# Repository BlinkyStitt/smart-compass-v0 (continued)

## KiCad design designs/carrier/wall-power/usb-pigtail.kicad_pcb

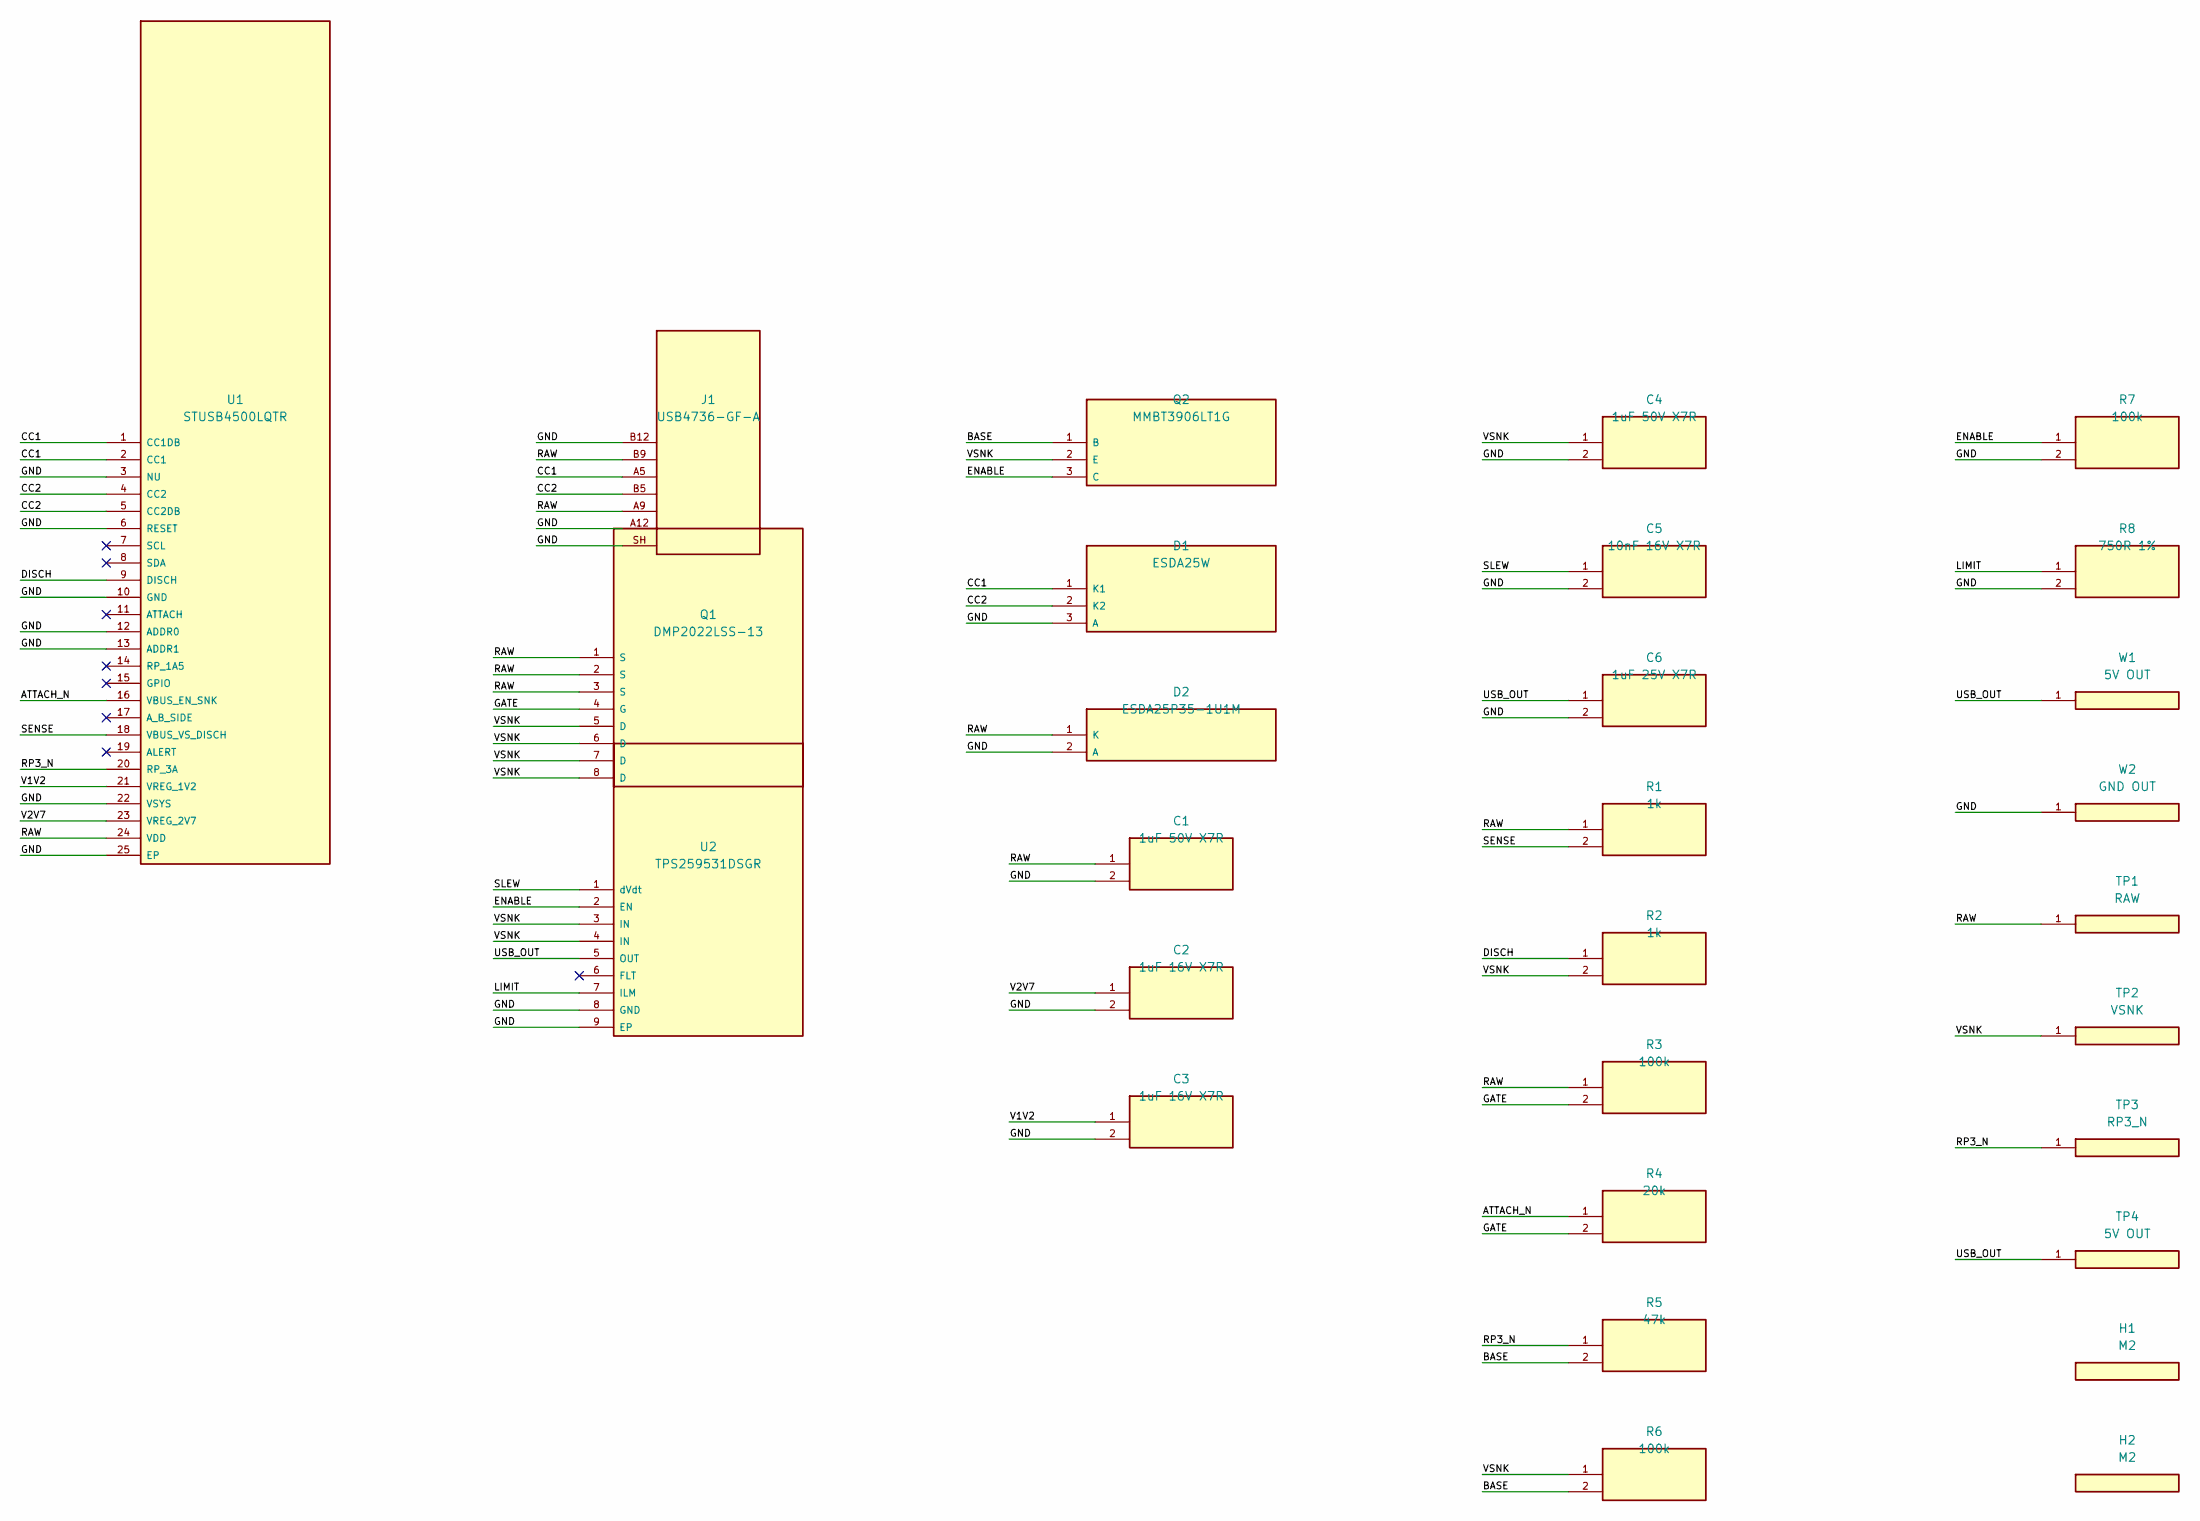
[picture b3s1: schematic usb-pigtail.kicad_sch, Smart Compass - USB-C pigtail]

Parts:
C1, C4: 1uF 50V X7R; C_0805_2012Metric
C2, C3: 1uF 16V X7R; C_0603_1608Metric
C5: 10nF 16V X7R; C_0603_1608Metric
C6: 1uF 25V X7R; C_0805_2012Metric
D1: ESDA25W; SOT-323_SC-70
D2: ESDA25P35-1U1M; ST_QFN-2L_1.6x1mm
H1, H2: M2; MountingHole_2.2mm_M2
J1: USB4736-GF-A
Q1: DMP2022LSS-13; SOIC-8_3.9x4.9mm_P1.27mm
Q2: MMBT3906LT1G; SOT-23
R1, R2: 1k; R_0603_1608Metric
R3, R6, R7: 100k; R_0603_1608Metric
R4: 20k; R_0603_1608Metric
R5: 47k; R_0603_1608Metric
R8: 750R 1%; R_0603_1608Metric
TP1: RAW; TestPoint_Pad_D1.0mm
TP2: VSNK; TestPoint_Pad_D1.0mm
TP3: RP3_N; TestPoint_Pad_D1.0mm
TP4: 5V OUT; TestPoint_Pad_D1.0mm
U1: STUSB4500LQTR; QFN-24-1EP_4x4mm_P0.5mm_EP2.7x2.7mm
U2: TPS259531DSGR; Texas_DSG0008A_WSON-8-1EP_2x2mm_P0.5mm_EP0.9x1.6mm
W1: 5V OUT; Lead_22AWG
W2: GND OUT; Lead_22AWG

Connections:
/ATTACH_N: R4.1, U1.16 (VBUS_EN_SNK)
/BASE: Q2.1 (B), R5.2, R6.2
/CC1: D1.1 (K1), J1.A5, U1.1 (CC1DB), U1.2 (CC1)
/CC2: D1.2 (K2), J1.B5, U1.4 (CC2), U1.5 (CC2DB)
/DISCH: R2.1, U1.9 (DISCH)
/ENABLE: Q2.3 (C), R7.1, U2.2 (EN)
/GATE: Q1.4 (G), R3.2, R4.2
/GND: C1.2, C2.2, C3.2, C4.2, C5.2, C6.2, D1.3 (A), D2.2 (A), J1.A12, J1.B12, J1.SH, R7.2, R8.2, U1.3 (NU), U1.6 (RESET), U1.10 (GND), U1.12 (ADDR0), U1.13 (ADDR1), U1.22 (VSYS), U1.25 (EP), U2.8 (GND), U2.9 (EP), W2.1
/LIMIT: R8.1, U2.7 (ILM)
/RAW: C1.1, D2.1 (K), J1.A9, J1.B9, Q1.1 (S), Q1.2 (S), Q1.3 (S), R1.1, R3.1, TP1.1, U1.24 (VDD)
/RP3_N: R5.1, TP3.1, U1.20 (RP_3A)
/SENSE: R1.2, U1.18 (VBUS_VS_DISCH)
/SLEW: C5.1, U2.1 (dVdt)
/USB_OUT: C6.1, TP4.1, U2.5 (OUT), W1.1
/V1V2: C3.1, U1.21 (VREG_1V2)
/V2V7: C2.1, U1.23 (VREG_2V7)
/VSNK: C4.1, Q1.5 (D), Q1.6 (D), Q1.7 (D), Q1.8 (D), Q2.2 (E), R2.2, R6.1, TP2.1, U2.3 (IN), U2.4 (IN)

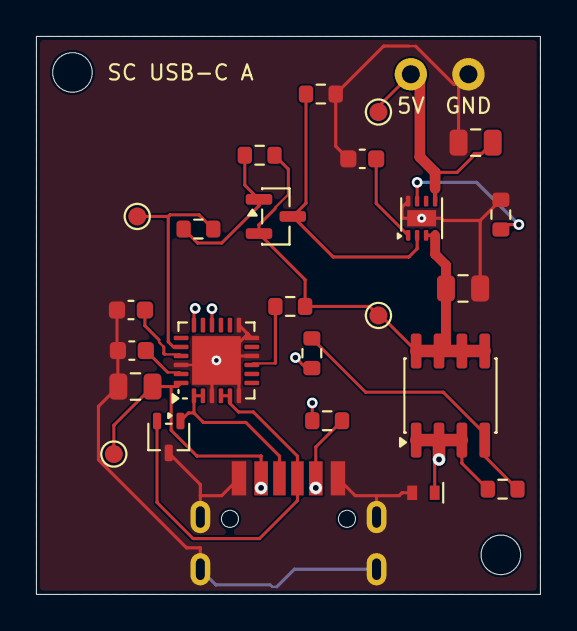
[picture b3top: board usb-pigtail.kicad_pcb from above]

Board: 4 copper layers, 28.0 x 31.0 mm, 29 parts (0 on the bottom side), 17 nets.

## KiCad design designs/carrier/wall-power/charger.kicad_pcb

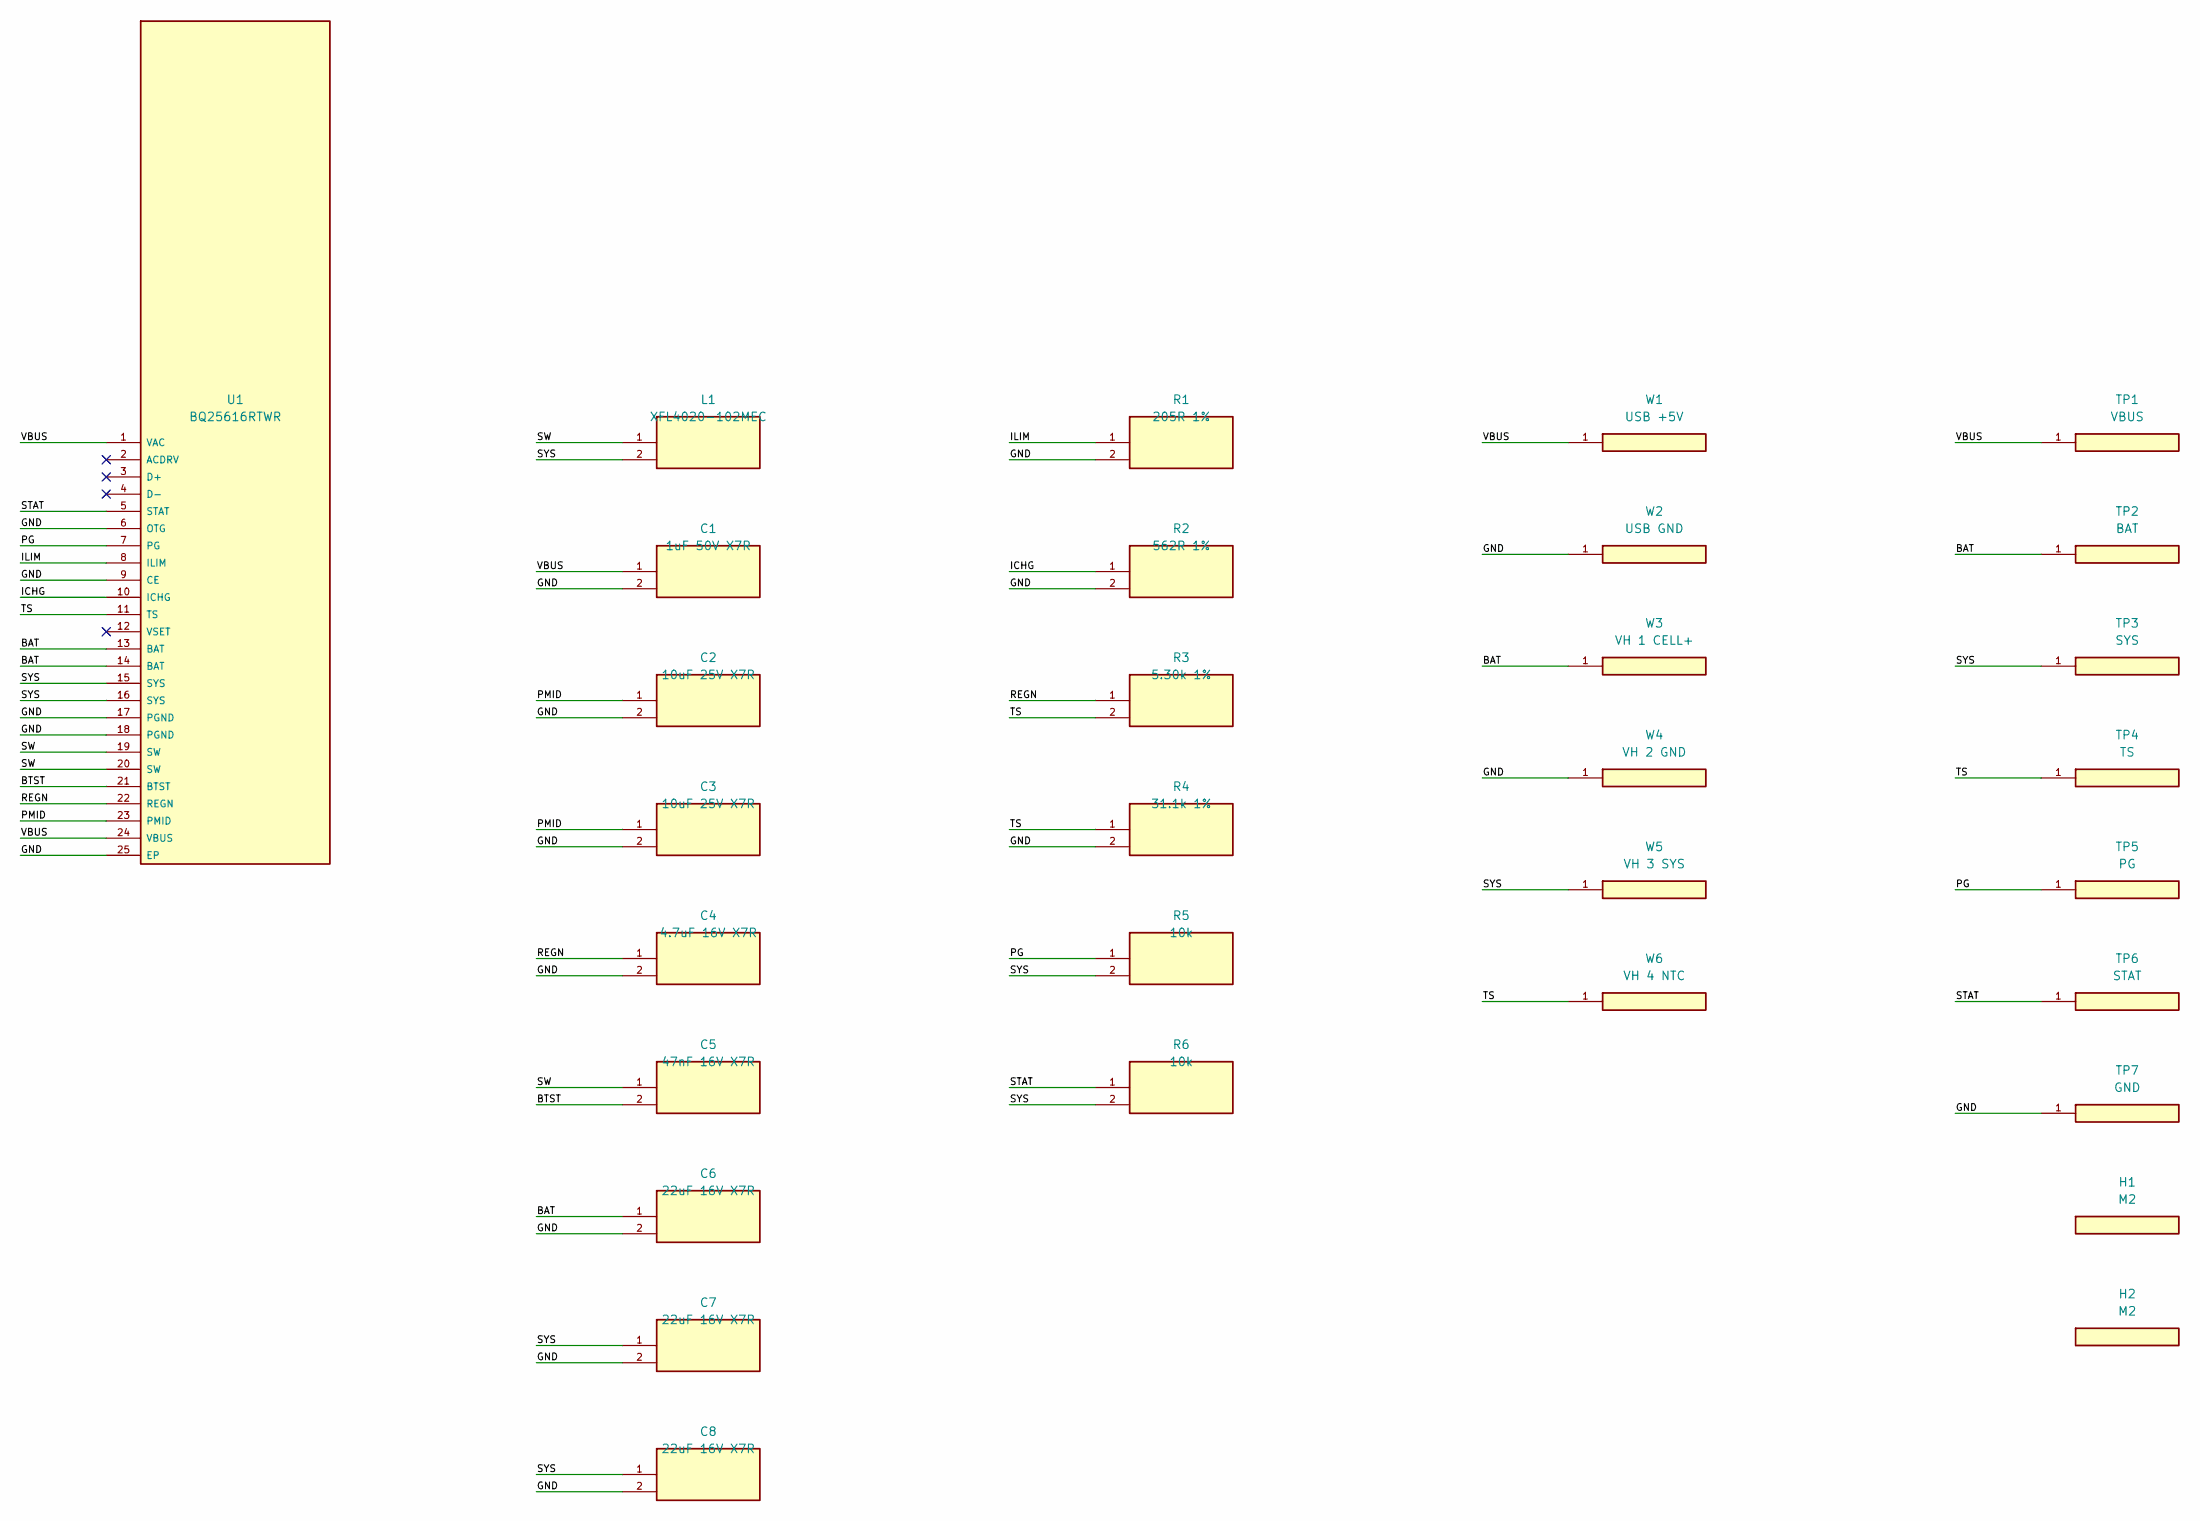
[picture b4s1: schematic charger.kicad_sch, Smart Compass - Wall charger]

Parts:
C1: 1uF 50V X7R; C_0805_2012Metric
C2, C3: 10uF 25V X7R; C_1206_3216Metric
C4: 4.7uF 16V X7R; C_0805_2012Metric
C5: 47nF 16V X7R; C_0603_1608Metric
C6, C7, C8: 22uF 16V X7R; C_1206_3216Metric
H1, H2: M2; MountingHole_2.2mm_M2
L1: XFL4020-102MEC; L_Coilcraft_XxL4020
R1: 205R 1%; R_0603_1608Metric
R2: 562R 1%; R_0603_1608Metric
R3: 5.30k 1%; R_0603_1608Metric
R4: 31.1k 1%; R_0603_1608Metric
R5, R6: 10k; R_0603_1608Metric
TP1: VBUS; TestPoint_Pad_D1.0mm
TP2: BAT; TestPoint_Pad_D1.0mm
TP3: SYS; TestPoint_Pad_D1.0mm
TP4: TS; TestPoint_Pad_D1.0mm
TP5: PG; TestPoint_Pad_D1.0mm
TP6: STAT; TestPoint_Pad_D1.0mm
TP7: GND; TestPoint_Pad_D1.0mm
U1: BQ25616RTWR; Texas_RTW_WQFN-24-1EP_4x4mm_P0.5mm_EP2.7x2.7mm
W1: USB +5V; Lead_22AWG
W2: USB GND; Lead_22AWG
W3: VH 1 CELL+; Lead_22AWG
W4: VH 2 GND; Lead_22AWG
W5: VH 3 SYS; Lead_22AWG
W6: VH 4 NTC; Lead_22AWG

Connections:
/BAT: C6.1, TP2.1, U1.13 (BAT), U1.14 (BAT), W3.1
/BTST: C5.2, U1.21 (BTST)
/GND: C1.2, C2.2, C3.2, C4.2, C6.2, C7.2, C8.2, R1.2, R2.2, R4.2, TP7.1, U1.6 (OTG), U1.9 (CE), U1.17 (PGND), U1.18 (PGND), U1.25 (EP), W2.1, W4.1
/ICHG: R2.1, U1.10 (ICHG)
/ILIM: R1.1, U1.8 (ILIM)
/PG: R5.1, TP5.1, U1.7 (PG)
/PMID: C2.1, C3.1, U1.23 (PMID)
/REGN: C4.1, R3.1, U1.22 (REGN)
/STAT: R6.1, TP6.1, U1.5 (STAT)
/SW: C5.1, L1.1, U1.19 (SW), U1.20 (SW)
/SYS: C7.1, C8.1, L1.2, R5.2, R6.2, TP3.1, U1.15 (SYS), U1.16 (SYS), W5.1
/TS: R3.2, R4.1, TP4.1, U1.11 (TS), W6.1
/VBUS: C1.1, TP1.1, U1.1 (VAC), U1.24 (VBUS), W1.1

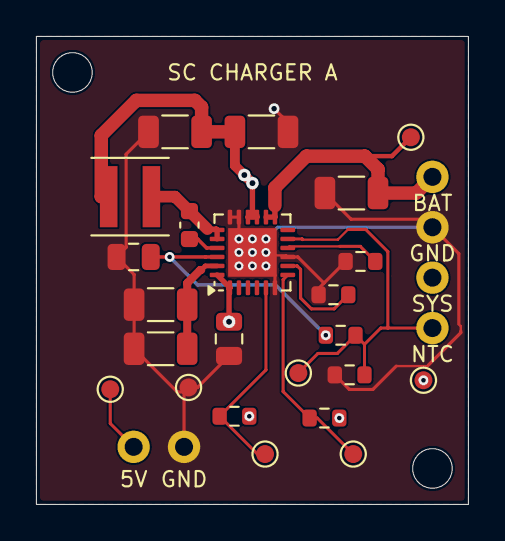
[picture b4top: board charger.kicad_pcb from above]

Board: 4 copper layers, 24.0 x 26.0 mm, 31 parts (0 on the bottom side), 13 nets.

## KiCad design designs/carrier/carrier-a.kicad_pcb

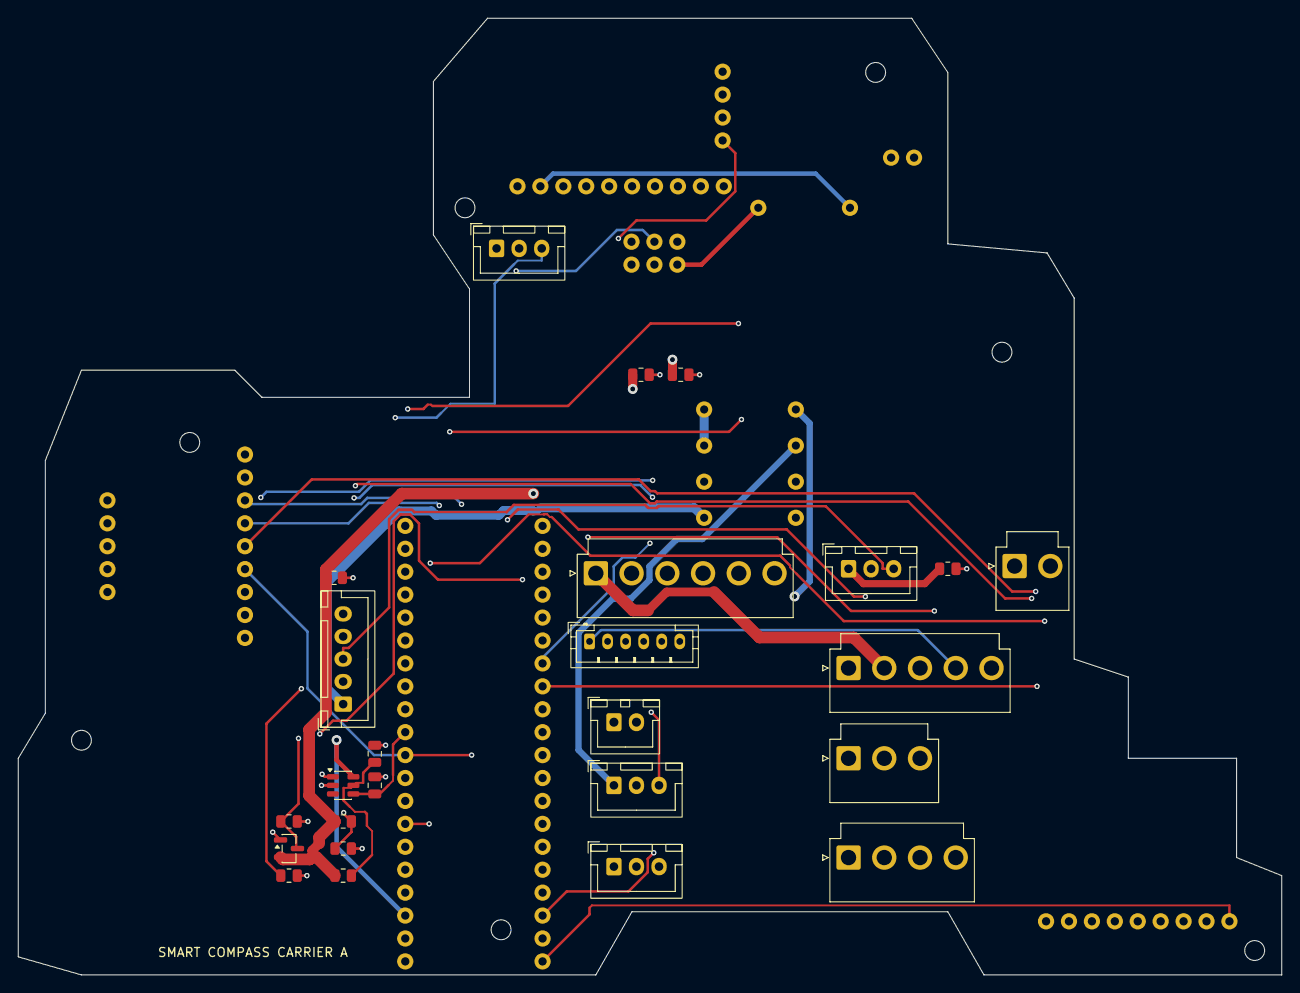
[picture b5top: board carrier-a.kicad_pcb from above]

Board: 4 copper layers, 140.0 x 106.0 mm, 42 parts (0 on the bottom side), 43 nets.

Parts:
BLACKPILL: BLACKPILL dock; BLACKPILL_dock
C1, C2: 100nF; C_0805_2012Metric
F1: 0251002.NRT1L; Axial_Fuse_251_P10.16mm
F2, F3, F4: 0251001.NRT1L; Axial_Fuse_251_P10.16mm
F5: 0251.500NRT1L; Axial_Fuse_251_P10.16mm
GPS: GPS dock; GPS_dock
H1, H2, H3, H4, H5, H6, H7: Carrier_mount
IMU: IMU dock; IMU_dock
J1: CHARGER; JST_VH_B4P-VH_1x04_P3.96mm_Vertical
J2: CELL; JST_VH_B3P-VH_1x03_P3.96mm_Vertical
J3: LATCH; JST_VH_B5P-VH_1x05_P3.96mm_Vertical
J4: BOOST; JST_VH_B6P-VH_1x06_P3.96mm_Vertical
J5: OUTPUT SWITCH; JST_XH_B2B-XH-A_1x02_P2.50mm_Vertical
J6: SPARKLE BARREL; JST_VH_B2P-VH_1x02_P3.96mm_Vertical
J7: SPARKLE JP1; JST_XH_B5B-XH-A_1x05_P2.50mm_Vertical
J8: FIBONACCI; JST_XH_B3B-XH-A_1x03_P2.50mm_Vertical
J9: INNER; JST_XH_B3B-XH-A_1x03_P2.50mm_Vertical
J10: SIDE A; JST_XH_B3B-XH-A_1x03_P2.50mm_Vertical
J11: SIDE B; JST_XH_B3B-XH-A_1x03_P2.50mm_Vertical
J12: BUTTONS; JST_PH_B6B-PH-K_1x06_P2.00mm_Vertical
Q1: MMBT3906; SOT-23
R1: 47k; R_0805_2012Metric
R2: 100k; R_0805_2012Metric
R3, R4: 100k 1%; R_0805_2012Metric
R5, R6, R7, R8: 1k; R_0805_2012Metric
R9: 100R; R_0805_2012Metric
RADIO: RADIO dock; RADIO_dock
SPARKLE: SPARKLE dock; SPARKLE_dock
U1: TS5A3160DBVR; SOT-23-6

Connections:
ACTION: BLACKPILL.P2.3, J12.5
AUX_3V3: BLACKPILL.P1.3, F5.2, GPS.JP4.9, IMU.JP4.9, RADIO.JP3.1, U1.6
AUX_SOURCE: F5.1, SPARKLE.JP3.2
BOOST_IN: J3.2, J4.1, Q1.2, R3.1, R7.1, R9.1
BOOST_OUT: J4.3, J5.1, R5.1
CELL_SW: J1.1, J2.1
FIB_5V: F1.2, J8.1, R8.1
GND: BLACKPILL.P1.2, C1.2, C2.2, GPS.JP4.7, IMU.JP4.7, J1.2, J2.2, J3.3, J4.2, J4.4, J6.2, J7.2, J8.2, J9.2, J10.2, J11.2, J12.2, J12.4, J12.6, R2.2, R4.2, R5.2, R6.2, R7.2, R8.2, RADIO.JP3.2, SPARKLE.JP3.1, U1.2
GPS_ENABLE: BLACKPILL.P2.15, GPS.JP1.4
GPS_PPS: BLACKPILL.P1.15, GPS.JP1.3
GPS_RX: BLACKPILL.P1.13, GPS.JP3.1
GPS_TX: BLACKPILL.P1.12, GPS.JP3.2
IMU_AG_READY: BLACKPILL.P1.4, IMU.JP2.3
IMU_AG_SELECT: BLACKPILL.P2.5, IMU.JP4.4
IMU_M_READY: BLACKPILL.P1.6, IMU.JP2.4
IMU_M_SELECT: BLACKPILL.P2.6, IMU.JP4.3
LATCH_OFF: J3.5, Q1.3, R2.1
LBO: J4.5, R1.1
LBO_BASE: Q1.1, R1.2
LED_DATA1: J7.3, J8.3
LED_DATA2: J7.4, J9.3
LED_DATA3: J7.5, J10.3
LED_DATA4: J11.3, SPARKLE.JP3.6
LED_DISTRIBUTION: F1.1, F2.1, F3.1, F4.1, J7.1
LOAD_5V: J5.2, J6.1, R6.1
MODE: BLACKPILL.P2.2, J12.3
RADIO_INTERRUPT: BLACKPILL.P2.13, RADIO.JP3.4
RADIO_RESET: BLACKPILL.P2.1, RADIO.JP3.9
RADIO_SELECT: BLACKPILL.P1.7, RADIO.JP3.8
RING1_5V: F2.2, J9.1
RING2_5V: F3.2, J10.1
RING3_5V: F4.2, J11.1
SENSE: BLACKPILL.P1.11, C1.1, U1.4
SENSE_DIV: R3.2, R4.1, U1.1
SENSE_VDD: C2.1, R9.2, U1.5
SPARKLE_RX: BLACKPILL.P2.14, SPARKLE.JP3.4
SPARKLE_TX: BLACKPILL.P2.7, SPARKLE.JP3.3
SPI_CLOCK: BLACKPILL.P1.10, IMU.JP4.6, RADIO.JP3.5
SPI_MISO: BLACKPILL.P1.9, IMU.JP4.1, IMU.JP4.2, RADIO.JP3.6
SPI_MOSI: BLACKPILL.P1.8, IMU.JP4.5, RADIO.JP3.7
START: J3.4, J12.1
SYS: J1.3, J3.1
THERM: J1.4, J2.3

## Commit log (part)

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2018-06-22 start adding a second light ring
2018-06-22 fix compass loops
2018-06-22 less flashlight density
2018-06-22 make clock work with 2 light rings
2018-06-22 simpler circle
2018-06-22 move sleep to afloop ter done transmitting
2018-06-25 format. fix flashligh. pins are partly working
2018-06-25 logging gps is broken. fix transmit
2018-06-25 tx compass pins
2018-06-25 no need for a return of bytes
2018-06-26 it compiles. still lots to do
2018-06-28 basics of showing saved compass pins
2018-06-28 add wip code
2018-06-28 improve framerate. debug print to figure out crash
2018-06-28 found the bug. now to fix it
2018-06-28 fix looping over ring size
2018-06-28 fix outer ring order
2018-06-28 test colors
2018-07-04 add types (and other stuff i forgot to commit)
2018-07-04 move more types
2018-07-04 fix type
2018-07-04 use internal rtc instead of timers
2018-07-04 better framerate and fix gps precision
2018-07-04 increase brightness
2018-07-04 rotate flashlight slower
2018-07-05 cleanup clock
2018-07-06 pretty lights, but it crashes sometimes
2018-07-06 update lights more often
    i haven't had it crash again, but plan on leaving it running overnight
2018-07-06 debug at full power
2018-07-07 minor tweaks
2018-07-07 skip the rtc
2018-07-07 lint and improve debug logging. not sure if this will crash eventually
2018-07-07 slow it down more. more power
2018-07-07 fix stutter
2018-07-07 comment
2018-07-09 don't wrap
2018-07-09 add missing return when clock is loading
2018-07-09 yellow instead of green
2018-07-09 faster pin saving
2018-07-10 seperate waiting and logging
2018-07-10 save some power
2018-07-10 use the constant
2018-07-10 i was wrong about charging
2018-07-10 lots of updateLights
2018-07-10 fade slower
2018-07-10 drop saturation. fade faster
2018-07-10 sleep is causing problems
2018-07-10 slower lights
2018-07-12 use INPUT_PULLUP for radio during tests
2018-08-16 less debug
2018-08-16 its partly working
2018-08-17 copy hue around differently
2018-08-20 change orientation in case
2018-08-21 my_file -> g_file
2018-08-21 i think these should be pointers
2018-08-21 fix pointers
2018-08-22 i new void star couldn't be right
2018-08-22 improve sync and fix compass. still crashes sometimes
2018-08-22 more offset
2018-08-22 check for memory leak
2018-08-22 fix orientation
2018-08-22 sending peer data is happy now that we are using pointers
2018-08-23 still crashing. lets just disable the radio stuff entirely for now
2018-08-23 fix off-by-one error in clock
2018-08-23 change getGPSTime to take a reference
2018-08-23 i dont know anymore
2018-08-23 maybe this is it
2018-08-23 add todo
2018-08-23 this isn' one potential crash. there is still another during radio tx
2018-08-24 sigh. i just needed to lower the light's power
2018-08-24 it seems to be working. lets let it run overnight
2018-08-24 less delay
2018-08-24 less lights
2018-08-24 i think this fixes crash on receive!
2018-08-24 read the sensor less and never during radio/gps processing
2018-08-25 interrupts!!!!!!!!!!!!!!!!!!!!!!!1
2023-08-25 Revert "interrupts!!!!!!!!!!!!!!!!!!!!!!!1"
    This reverts commit b79be3acf77d0a7e6d13b9dadb4fde4d3abdad96.
